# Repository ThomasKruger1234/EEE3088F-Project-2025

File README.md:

This repo contains the PCB design for the power distribution subsystem of a micromouse robot.

This design was created in fullfilment of the requirements of EEE3088F (UCT, 2025)

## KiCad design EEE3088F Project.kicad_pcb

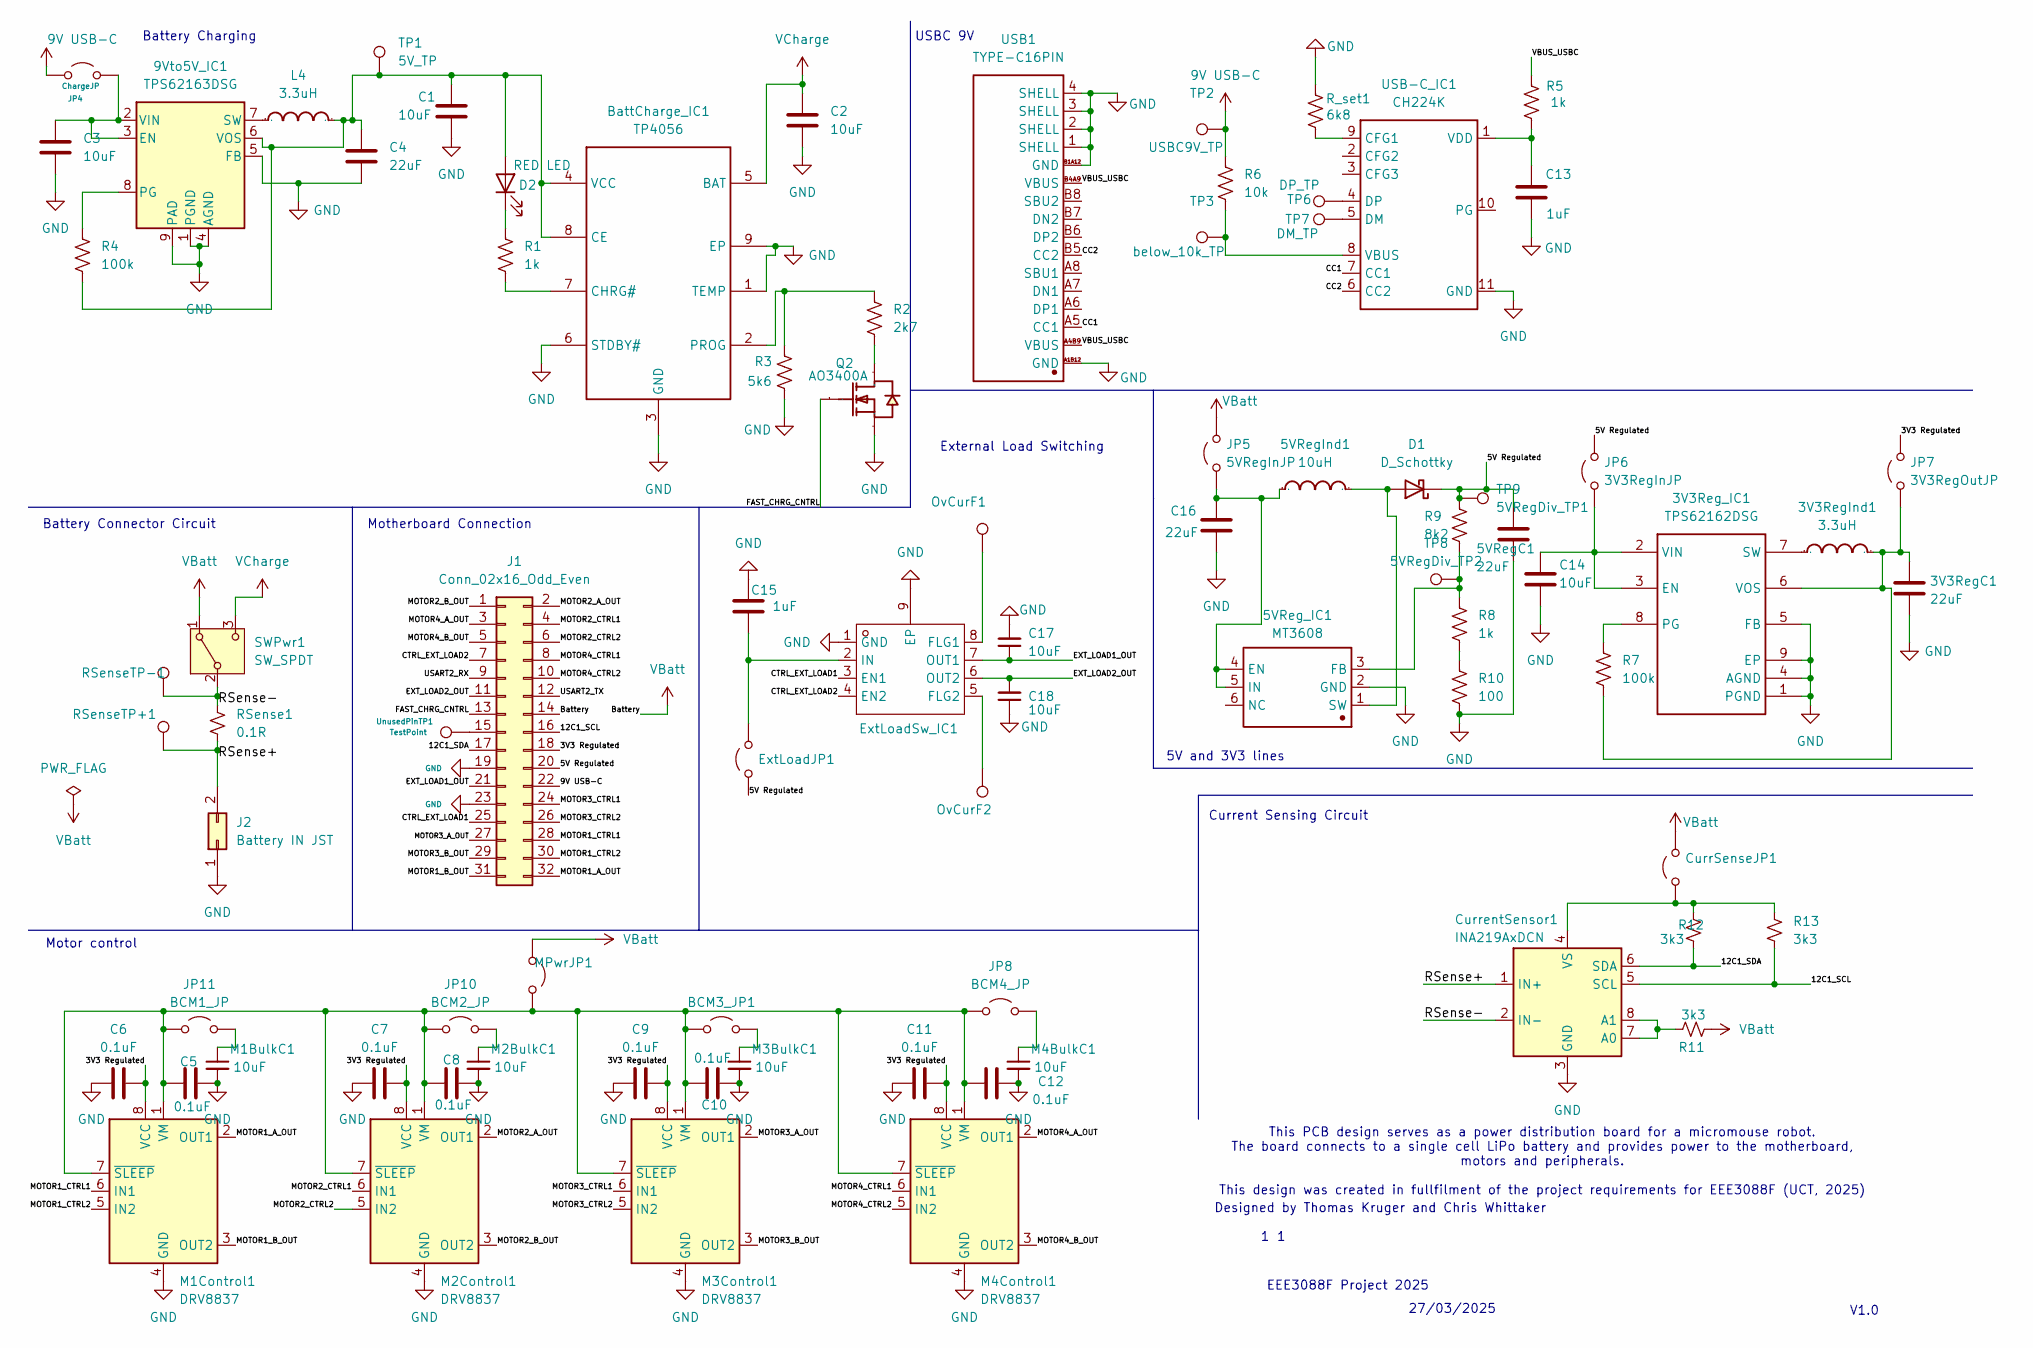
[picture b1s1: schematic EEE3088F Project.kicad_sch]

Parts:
3V3RegC1, 5VRegC1: 22uF; C_1206_3216Metric_Pad1.33x1.80mm_HandSolder
3V3RegInd1: 3.3uH; IND-SMD_L4.0-W4.0_FNR40XXS; Manufacturer Part FNR4030S3R3MT
3V3Reg_IC1: TPS62162DSG; WSON-8_L2.0-W2.0-P0.50-TL-EP; Manufacturer Part TPS62162DSGR
5VRegInd1: 10uH; IND-SMD_L7.8-W7.0-A; Manufacturer Part SM7850-100MT
5VReg_IC1: MT3608; SOT-23-6_L2.9-W1.6-P0.95-LS2.8-BL; Manufacturer Part MT3608
9Vto5V_IC1: TPS62163DSG; WSON-8_L2.0-W2.0-P0.50-TL-EP
BCM3_JP1: BCM3_JP; SolderJumper-2_P1.3mm_Open_Pad1.0x1.5mm
BattCharge_IC1: TP4056; ESOP-8_L4.9-W3.9-P1.27-LS6.0-BL-EP; Manufacturer Part TP4056-42-ESOP8
C1, C2, C3, C14, C17, C18: 10uF; C_0805_2012Metric_Pad1.18x1.45mm_HandSolder
C4, C16: 22uF; C_1206_3216Metric_Pad1.33x1.80mm_HandSolder
C5, C6, C7, C8, C9, C10, C11, C12: 0.1uF; C_0402_1005Metric_Pad0.74x0.62mm_HandSolder
C13, C15: 1uF; C_0603_1608Metric_Pad1.08x0.95mm_HandSolder
CurrSenseJP1: CurrentSenseJP; SolderJumper-2_P1.3mm_Open_Pad1.0x1.5mm
CurrentSensor1: INA219AxDCN; SOT-23-8
D1: D_Schottky; SMA_L4.3-W2.6-LS5.2-RD
D2: RED LED; LED_0805_2012Metric
ExtLoadJP1: ExtLoadJP; SolderJumper-2_P1.3mm_Open_Pad1.0x1.5mm
ExtLoadSw_IC1: MSOP-8_L3.0-W3.0-P0.65-LS4.9-BL-EP1.8; Manufacturer Part AP2192AMPG-13; LCSC Part Name Power Switch/Driver 1:2 P-Channel 1.5A 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
J1: Conn_02x16_Odd_Even; PinSocket_2x16_P2.54mm_Vertical
J2: Battery IN JST; PinSocket_1x02_P2.00mm_Vertical
JP4: ChargeJP; SolderJumper-2_P1.3mm_Open_Pad1.0x1.5mm
JP5: 5VRegInJP; SolderJumper-2_P1.3mm_Open_Pad1.0x1.5mm
JP6: 3V3RegInJP; SolderJumper-2_P1.3mm_Open_Pad1.0x1.5mm
JP7: 3V3RegOutJP; SolderJumper-2_P1.3mm_Open_Pad1.0x1.5mm
JP8: BCM4_JP; SolderJumper-2_P1.3mm_Open_Pad1.0x1.5mm
JP10: BCM2_JP; SolderJumper-2_P1.3mm_Open_Pad1.0x1.5mm
JP11: BCM1_JP; SolderJumper-2_P1.3mm_Open_Pad1.0x1.5mm
L4: 3.3uH; IND-SMD_L4.0-W4.0_FNR40XXS; Manufacturer Part FNR4030S3R3MT
M1BulkC1, M2BulkC1, M3BulkC1, M4BulkC1: 10uF; C_0805_2012Metric_Pad1.18x1.45mm_HandSolder
M1Control1, M2Control1, M3Control1, M4Control1: DRV8837; WSON-8-1EP_2x2mm_P0.5mm_EP0.9x1.6mm
MPwrJP1: MotorPWRJP; SolderJumper-2_P1.3mm_Open_Pad1.0x1.5mm
OvCurF1, OvCurF2: TestPoint; TestPoint_Pad_2.0x2.0mm
Q2: AO3400A; SOT-23-3_L2.9-W1.3-P1.90-LS2.4-BR; Manufacturer Part AO3400A
R1, R5, R8: 1k; R_0603_1608Metric_Pad0.98x0.95mm_HandSolder
R2: 2k7; R_0603_1608Metric_Pad0.98x0.95mm_HandSolder
R3: 5k6; R_0603_1608Metric_Pad0.98x0.95mm_HandSolder
R4, R7: 100k; R_0603_1608Metric_Pad0.98x0.95mm_HandSolder
R6: 10k; R_0603_1608Metric_Pad0.98x0.95mm_HandSolder
R9: 8k2; R_0603_1608Metric_Pad0.98x0.95mm_HandSolder
R10: 100; R_0603_1608Metric_Pad0.98x0.95mm_HandSolder
R11, R12, R13: 3k3; R_0603_1608Metric_Pad0.98x0.95mm_HandSolder
RSense1: 0.1R; R_1206_3216Metric_Pad1.30x1.75mm_HandSolder
RSenseTP+1: TestPoint; TestPoint_Pad_2.0x2.0mm
RSenseTP-1: TestPoint; TestPoint_Pad_2.0x2.0mm
R_set1: 6k8; R_0603_1608Metric_Pad0.98x0.95mm_HandSolder
SWPwr1: SW_SPDT; SW-TH_5P-P4.70_SS-12D11-G050
TP1: 5V_TP; TestPoint_Pad_2.0x2.0mm
TP2: USBC9V_TP; TestPoint_Pad_2.0x2.0mm
TP3: below_10k_TP; TestPoint_Pad_2.0x2.0mm
TP6: DP_TP; TestPoint_Pad_2.0x2.0mm
TP7: DM_TP; TestPoint_Pad_2.0x2.0mm
TP8: 5VRegDiv_TP2; TestPoint_Pad_2.0x2.0mm
TP9: 5VRegDiv_TP1; TestPoint_Pad_2.0x2.0mm
USB1: TYPE-C16PIN; USB-C-SMD_TYPE-C16PIN; Manufacturer Part TYPE-C16PIN
USB-C_IC1: CH224K; ESSOP-10_L4.9-W3.9-P1.0-LS6.0-TL-EP; Manufacturer Part CH224K
UnusedPinTP1: TestPoint; TestPoint_Pad_2.0x2.0mm

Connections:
9V USB-C: J1.22, JP4.1 (A), R6.1, TP2.1
/3V3 Regulated: C6.2, C7.2, C9.2, C11.2, J1.18, JP7.2 (B), M1Control1.8 (VCC), M2Control1.8 (VCC), M3Control1.8 (VCC), M4Control1.8 (VCC)
/5V Regulated: 5VRegC1.1, D1.1 (K), ExtLoadJP1.1 (A), J1.20, JP6.2 (B), R9.1, TP9.1; also elsewhere on the board
/12C1_SCL: CurrentSensor1.5 (SCL), J1.16, R13.2
/12C1_SDA: CurrentSensor1.6 (SDA), J1.17, R12.2
/CC1: USB1.A5 (CC1), USB-C_IC1.7 (CC1)
/CC2: USB1.B5 (CC2), USB-C_IC1.6 (CC2)
/CTRL_EXT_LOAD1: ExtLoadSw_IC1.3 (EN1), J1.25
/CTRL_EXT_LOAD2: ExtLoadSw_IC1.4 (EN2), J1.7
/EXT_LOAD1_OUT: C17.1, ExtLoadSw_IC1.7 (OUT1), J1.21
/EXT_LOAD2_OUT: C18.2, ExtLoadSw_IC1.6 (OUT2), J1.11
/FAST_CHRG_CNTRL: J1.13, Q2.1 (G)
/MOTOR1_A_OUT: J1.32, M1Control1.2 (OUT1)
/MOTOR1_B_OUT: J1.31, M1Control1.3 (OUT2)
/MOTOR1_CTRL1: J1.28, M1Control1.6 (IN1)
/MOTOR1_CTRL2: J1.30, M1Control1.5 (IN2)
/MOTOR2_A_OUT: J1.2, M2Control1.2 (OUT1)
/MOTOR2_B_OUT: J1.1, M2Control1.3 (OUT2)
/MOTOR2_CTRL1: J1.4, M2Control1.6 (IN1)
/MOTOR2_CTRL2: J1.6, M2Control1.5 (IN2)
/MOTOR3_A_OUT: J1.27, M3Control1.2 (OUT1)
/MOTOR3_B_OUT: J1.29, M3Control1.3 (OUT2)
/MOTOR3_CTRL1: J1.24, M3Control1.6 (IN1)
/MOTOR3_CTRL2: J1.26, M3Control1.5 (IN2)
/MOTOR4_A_OUT: J1.3, M4Control1.2 (OUT1)
/MOTOR4_B_OUT: J1.5, M4Control1.3 (OUT2)
/MOTOR4_CTRL1: J1.8, M4Control1.6 (IN1)
/MOTOR4_CTRL2: J1.10, M4Control1.5 (IN2)
/RSense+: CurrentSensor1.1 (IN+), J2.2, RSense1.2, RSenseTP+1.1
/RSense-: CurrentSensor1.2 (IN-), RSense1.1, RSenseTP-1.1, SWPwr1.2 (B)
/USART2_RX: J1.9
/USART2_TX: J1.12
/VBUS_USBC: R5.1, USB1.A4B9 (VBUS), USB1.B4A9 (VBUS)
GND: 3V3RegC1.2, 3V3Reg_IC1.1 (PGND), 3V3Reg_IC1.4 (AGND), 3V3Reg_IC1.5 (FB), 3V3Reg_IC1.9 (EP), 5VRegC1.2, 5VReg_IC1.2 (GND), 9Vto5V_IC1.1 (PGND), 9Vto5V_IC1.4 (AGND), 9Vto5V_IC1.5 (FB), 9Vto5V_IC1.9 (PAD), BattCharge_IC1.1 (TEMP), BattCharge_IC1.3 (GND), BattCharge_IC1.6 (STDBY#), BattCharge_IC1.9 (EP), C1.1, C2.2, C3.2, C4.2, C5.2, C6.1, C7.1, C8.2, C9.1, C10.2, C11.1, C12.2, C13.2, C14.2, C15.2, C16.2, C17.2, C18.1, CurrentSensor1.3 (GND), ExtLoadSw_IC1.1 (GND), ExtLoadSw_IC1.9 (EP), J1.19, J1.23, J2.1, M1BulkC1.2, M1Control1.4 (GND), M1Control1.9 (GND), M2BulkC1.2, M2Control1.4 (GND), M2Control1.9 (GND), M3BulkC1.2, M3Control1.4 (GND), M3Control1.9 (GND), M4BulkC1.2, M4Control1.4 (GND), M4Control1.9 (GND), Q2.2 (S), R3.2, R10.2, R_set1.2, USB1.1 (SHELL), USB1.2 (SHELL), USB1.3 (SHELL), USB1.4 (SHELL), USB1.A1B12 (GND), USB1.B1A12 (GND), USB-C_IC1.11 (GND)
unnamed: 3V3Reg_IC1.2 (VIN), 3V3Reg_IC1.3 (EN), C14.1, JP6.1 (A)
unnamed: 3V3Reg_IC1.8 (PG), R7.1
unnamed: 3V3RegInd1.1, 3V3Reg_IC1.7 (SW)
unnamed: 3V3RegC1.1, 3V3RegInd1.2, 3V3Reg_IC1.6 (VOS), JP7.1 (A), R7.2
unnamed: 5VRegInd1.1, 5VReg_IC1.4 (EN), 5VReg_IC1.5 (IN), C16.1, JP5.1 (A)
unnamed: 5VReg_IC1.3 (FB), R8.1, R9.2, TP8.1
unnamed: 5VRegInd1.2, 5VReg_IC1.1 (SW), D1.2 (A)
unnamed: 9Vto5V_IC1.2 (VIN), 9Vto5V_IC1.3 (EN), C3.1, JP4.2 (B)
unnamed: 9Vto5V_IC1.8 (PG), R4.1
unnamed: 9Vto5V_IC1.7 (SW), L4.1
unnamed: 9Vto5V_IC1.6 (VOS), BattCharge_IC1.4 (VCC), BattCharge_IC1.8 (CE), C1.2, C4.1, D2.2 (A), L4.2, R4.2, TP1.1
unnamed: BCM3_JP1.1 (A), C5.1, C8.1, C10.1, C12.1, JP8.1 (A), JP10.1 (A), JP11.1 (A), M1Control1.1 (VM), M1Control1.7 (~SLEEP), M2Control1.1 (VM), M2Control1.7 (~SLEEP), M3Control1.1 (VM), M3Control1.7 (~SLEEP), M4Control1.1 (VM), M4Control1.7 (~SLEEP), MPwrJP1.2 (B)
unnamed: BCM3_JP1.2 (B), M3BulkC1.1
unnamed: BattCharge_IC1.7 (CHRG#), R1.2
unnamed: BattCharge_IC1.2 (PROG), R2.1, R3.1
unnamed: CurrSenseJP1.1 (A), CurrentSensor1.4 (VS), R12.1, R13.1
unnamed: CurrentSensor1.7 (A0), CurrentSensor1.8 (A1), R11.1
unnamed: D2.1 (K), R1.1
unnamed: C15.1, ExtLoadJP1.2 (B), ExtLoadSw_IC1.2 (IN)
unnamed: ExtLoadSw_IC1.8 (FLG1), OvCurF1.1
unnamed: ExtLoadSw_IC1.5 (FLG2), OvCurF2.1
unnamed: J1.15, UnusedPinTP1.1
unnamed: JP8.2 (B), M4BulkC1.1
unnamed: JP10.2 (B), M2BulkC1.1
unnamed: JP11.2 (B), M1BulkC1.1
unnamed: Q2.3 (D), R2.2
unnamed: R8.2, R10.1
unnamed: R_set1.1, USB-C_IC1.9 (CFG1)
unnamed: TP7.1, USB-C_IC1.5 (DM)
unnamed: TP6.1, USB-C_IC1.4 (DP)
unnamed: R6.2, TP3.1, USB-C_IC1.8 (VBUS)
unnamed: C13.1, R5.2, USB-C_IC1.1 (VDD)
VBatt: CurrSenseJP1.2 (B), J1.14, JP5.2 (B), MPwrJP1.1 (A), R11.2, SWPwr1.1 (A)
VCharge: BattCharge_IC1.5 (BAT), C2.1, SWPwr1.3 (C)

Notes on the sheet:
Motor control
27/03/2025
External Load Switching
V1.0
USBC 9V
Battery Charging
Battery Connector Circuit
5V and 3V3 lines
EEE3088F Project 2025
Motherboard Connection
Designed by Thomas Kruger and Chris Whittaker
Current Sensing Circuit
This PCB design serves as a power distribution board for a micromouse robot. The board connects to a single cell LiPo battery and provides power to the motherboard, motors and peripherals. This design was created in fullfilment of the project requirements for EEE3088F (UCT, 2025)

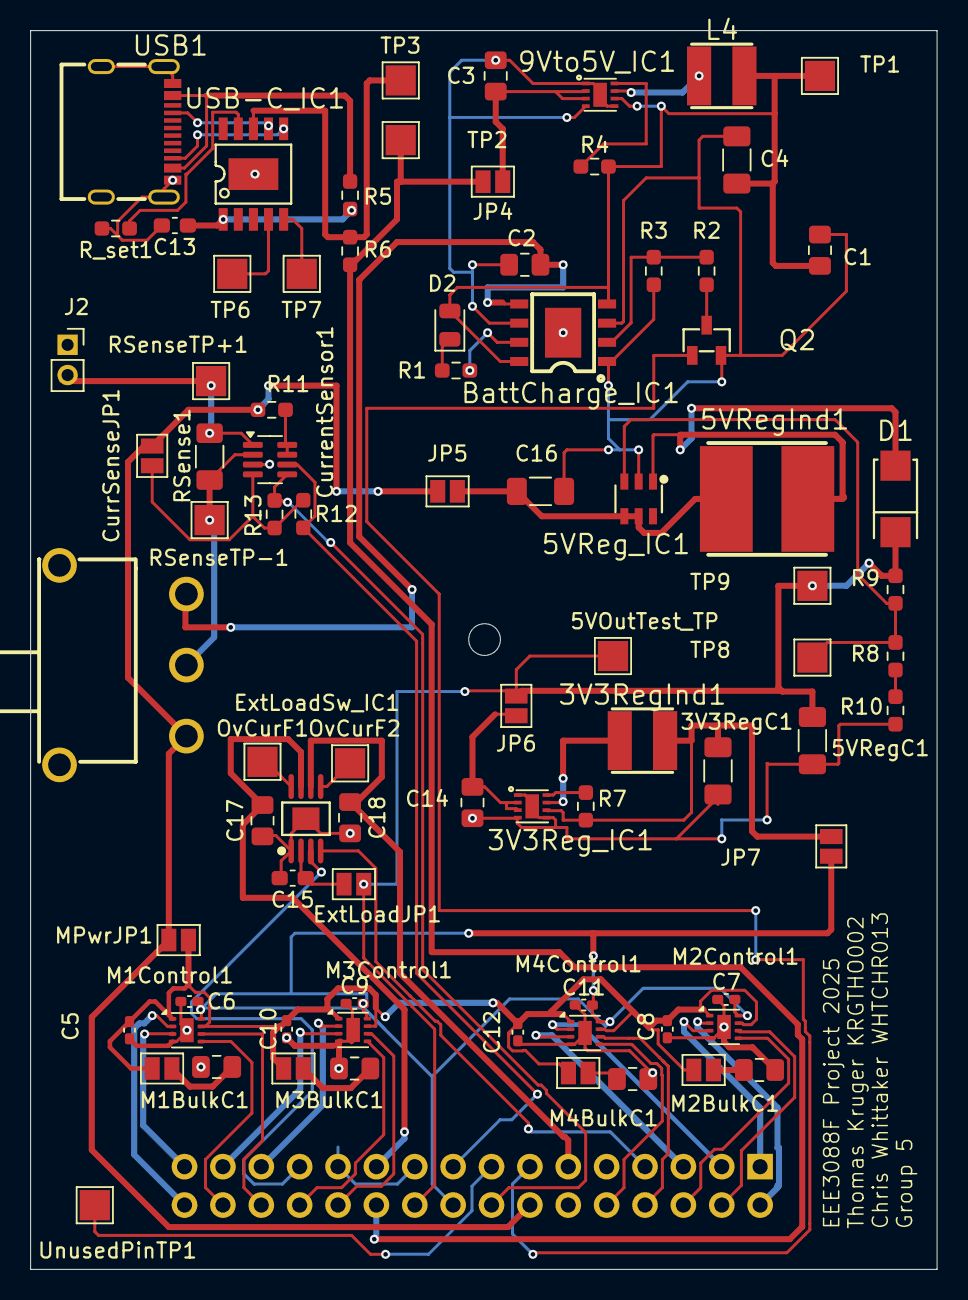
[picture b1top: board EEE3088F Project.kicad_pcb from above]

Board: 2 copper layers, 60.0 x 82.0 mm, 84 parts (1 on the bottom side), 66 nets.

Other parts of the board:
5VOutTest_TP: 5V_out_test; TestPoint_Pad_2.0x2.0mm

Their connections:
/5V Regulated: 5VOutTest_TP.1; also elsewhere on the board

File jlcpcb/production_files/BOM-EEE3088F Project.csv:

Comment,Designator,Footprint,LCSC,Quantity
22uF,"3V3RegC1,5VRegC1,C16,C4",C_1206_3216Metric_Pad1.33x1.80mm_HandSolder,C12891,4
2k7,R2,R_0603_1608Metric_Pad0.98x0.95mm_HandSolder,C13167,1
0.1uF,"C10,C11,C12,C5,C6,C7,C8,C9",C_0402_1005Metric_Pad0.74x0.62mm_HandSolder,C1525,8
10uF,"C1,C14,C17,C18,C2,C3,M1BulkC1,M2BulkC1,M3BulkC1,M4BulkC1",C_0805_2012Metric_Pad1.18x1.45mm_HandSolder,C15850,10
1uF,"C13,C15",C_0603_1608Metric_Pad1.08x0.95mm_HandSolder,C1592,2
TP4056,BattCharge_IC1,ESOP-8_L4.9-W3.9-P1.27-LS6.0-BL-EP,C16581,1
3.3uH,"3V3RegInd1,L4",IND-SMD_L4.0-W4.0_FNR40XXS,C167870,2
SW_SPDT,SWPwr1,SW-TH_5P-P4.70_SS-12D11-G050,C17179528,1
AO3400A,Q2,SOT-23-3_L2.9-W1.3-P1.90-LS2.4-BR,C20917,1
1k,"R1,R5,R8",R_0603_1608Metric_Pad0.98x0.95mm_HandSolder,C21190,3
100,R10,R_0603_1608Metric_Pad0.98x0.95mm_HandSolder,C22775,1
RED LED,D2,LED_0805_2012Metric,C2297,1
3k3,"R11,R12,R13",R_0603_1608Metric_Pad0.98x0.95mm_HandSolder,C22978,3
5k6,R3,R_0603_1608Metric_Pad0.98x0.95mm_HandSolder,C23189,1
6k8,R_set1,R_0603_1608Metric_Pad0.98x0.95mm_HandSolder,C23212,1
0.1R,RSense1,R_1206_3216Metric_Pad1.30x1.75mm_HandSolder,C25334,1
100k,"R4,R7",R_0603_1608Metric_Pad0.98x0.95mm_HandSolder,C25803,2
10k,R6,R_0603_1608Metric_Pad0.98x0.95mm_HandSolder,C25804,1
8k2,R9,R_0603_1608Metric_Pad0.98x0.95mm_HandSolder,C25981,1
DRV8837,"M1Control1,M2Control1,M3Control1,M4Control1",WSON-8-1EP_2x2mm_P0.5mm_EP0.9x1.6mm,C39159,4
TYPE-C16PIN,USB1,USB-C-SMD_TYPE-C16PIN,C393939,1
TPS62162DSG,3V3Reg_IC1,WSON-8_L2.0-W2.0-P0.50-TL-EP,C40256,1
~,ExtLoadSw_IC1,MSOP-8_L3.0-W3.0-P0.65-LS4.9-BL-EP1.8,C507872,1
MT3608,5VReg_IC1,SOT-23-6_L2.9-W1.6-P0.95-LS2.8-BL,C84817,1
D_Schottky,D1,SMA_L4.3-W2.6-LS5.2-RD,C8678,1
INA219AxDCN,CurrentSensor1,SOT-23-8,C87469,1
10uH,5VRegInd1,IND-SMD_L7.8-W7.0-A,C9182,1
TPS62163DSG,9Vto5V_IC1,WSON-8_L2.0-W2.0-P0.50-TL-EP,C97534,1
CurrentSenseJP,CurrSenseJP1,SolderJumper-2_P1.3mm_Open_Pad1.0x1.5mm,,1
below_10k_TP,TP3,TestPoint_Pad_2.0x2.0mm,,1
ExtLoadJP,ExtLoadJP1,SolderJumper-2_P1.3mm_Open_Pad1.0x1.5mm,,1
DM_TP,TP7,TestPoint_Pad_2.0x2.0mm,,1
BCM3_JP,BCM3_JP1,SolderJumper-2_P1.3mm_Open_Pad1.0x1.5mm,,1
TestPoint,OvCurF2,TestPoint_Pad_2.0x2.0mm,,1
5VRegDiv_TP1,TP9,TestPoint_Pad_2.0x2.0mm,,1
BCM2_JP,JP10,SolderJumper-2_P1.3mm_Open_Pad1.0x1.5mm,,1
Battery IN JST,J2,PinSocket_1x02_P2.00mm_Vertical,,1
TestPoint,UnusedPinTP1,TestPoint_Pad_2.0x2.0mm,,1
BCM1_JP,JP11,SolderJumper-2_P1.3mm_Open_Pad1.0x1.5mm,,1
3V3RegOutJP,JP7,SolderJumper-2_P1.3mm_Open_Pad1.0x1.5mm,,1
5V_TP,TP1,TestPoint_Pad_2.0x2.0mm,,1
DP_TP,TP6,TestPoint_Pad_2.0x2.0mm,,1
5VRegDiv_TP2,TP8,TestPoint_Pad_2.0x2.0mm,,1
USBC9V_TP,TP2,TestPoint_Pad_2.0x2.0mm,,1
ChargeJP,JP4,SolderJumper-2_P1.3mm_Open_Pad1.0x1.5mm,,1
BCM4_JP,JP8,SolderJumper-2_P1.3mm_Open_Pad1.0x1.5mm,,1
5VRegInJP,JP5,SolderJumper-2_P1.3mm_Open_Pad1.0x1.5mm,,1
TestPoint,OvCurF1,TestPoint_Pad_2.0x2.0mm,,1
MotorPWRJP,MPwrJP1,SolderJumper-2_P1.3mm_Open_Pad1.0x1.5mm,,1
3V3RegInJP,JP6,SolderJumper-2_P1.3mm_Open_Pad1.0x1.5mm,,1
Conn_02x16_Odd_Even,J1,PinSocket_2x16_P2.54mm_Vertical,,1

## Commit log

2025-03-21 Created KiCad file and added pin headers
2025-03-21 test push/pull
2025-03-21 added battery charging subsection (no footprints yet)
2025-03-21 Added motor driver circuits and footprints
2025-03-22 started on current sensing circuit
2025-03-22 changed battery charging circuit's buck converter and added mosfet circuit for charging mode selection
2025-03-23 Finished current sensor circuit, finished battery connector circuit. Added footprints and BOM info for all.
2025-03-23 added 3V3 and 5V out circuitry as well as USBC
2025-03-23 removed gerbers generated by mistake
2025-03-24 corrected footprints for usbc and schottky diode
2025-03-24 added custom symbol and placed usbc and schottky custom footprints into custom footprints.pretty
2025-03-24 Cleaned up battery charging circuit and added Battery, 3V3_out and 5V_out labels to motherboard connection
2025-03-24 Added external load switching circuit
2025-03-25 checked footprints and finished BOM for my components
2025-03-25 Fixed BOM
2025-03-25 changed inductors
2025-03-27 Routed Thomas half of PCB traces. Minor labelling modifications in schematic.
2025-03-27 finished routing
2025-03-27 added and fixed traces and trace widths. Fixed design rule check errors
2025-03-27 Minor labelling fixes. Generated gerber files
2025-03-28 ensuring all changes committed
2025-03-28 added thicker lines for 9V, 5V, VBatt and 3V3
2025-03-28 Finishing touches + mounting hole
2025-03-28 Added submission zip file
